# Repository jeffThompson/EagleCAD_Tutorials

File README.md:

EagleCAD Tutorials
==================

A set of tutorials for learning EagleCAD and circuit design.

####DRU FILE
Also included is a design rule set called 'BasicHandEtching.dru', designed for home PCB etching using laser printed overhead transparencies and ferric chloride. To install this file, download it and place it in:

    Applications > Eagle > dru

####PCB ETCHING IMAGE
This repository also includes a file called 'PCB_EtchingImage.png' - this file has undergone several transformations after export from Eagle:
1. Colors inverted - I use a MG Chemicals 600 series boards which are positive sensitized. Areas that are white are exposed and etched away, so the image from Eagle must be inverted.
2. The image is flipped - this means that when printed on overhead transparency film the printed image will be face-down, ensuring no light leaks under the printed image.

\- \- \-

\[ all code available under [Creative Commons BY-NC-SA license](http://creativecommons.org/licenses/by-nc-sa/3.0/) - feel free to use but [please let me know](http://www.jeffreythompson.org) \]

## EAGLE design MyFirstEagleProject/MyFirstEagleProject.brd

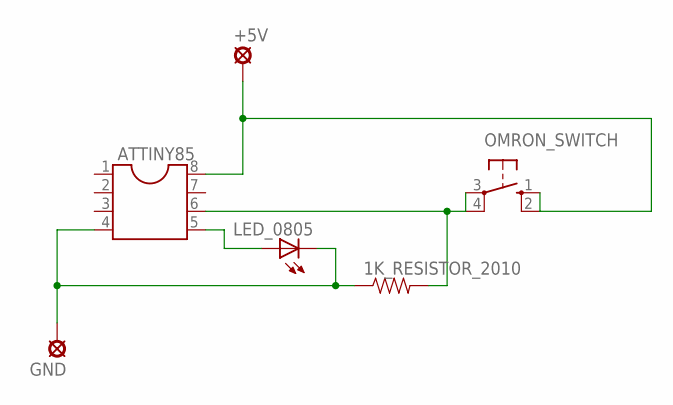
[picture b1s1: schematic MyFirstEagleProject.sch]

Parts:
1K_RESISTOR_2010: RESISTOR2010; R2010
+5V: SE14
ATTINY85: DIL8S; SOCKET-08
GND: SE14
LED_0805: LEDCHIPLED_0805; CHIPLED_0805
OMRON_SWITCH: 10-XX; B3F-10XX

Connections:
5V: +5V.MP, ATTINY85.8, OMRON_SWITCH.1 (S), OMRON_SWITCH.2 (S1)
GND: 1K_RESISTOR_2010.1, ATTINY85.4, GND.MP, LED_0805.C
unnamed: ATTINY85.5, LED_0805.A
unnamed: 1K_RESISTOR_2010.2, ATTINY85.6, OMRON_SWITCH.3, OMRON_SWITCH.4 (P1)

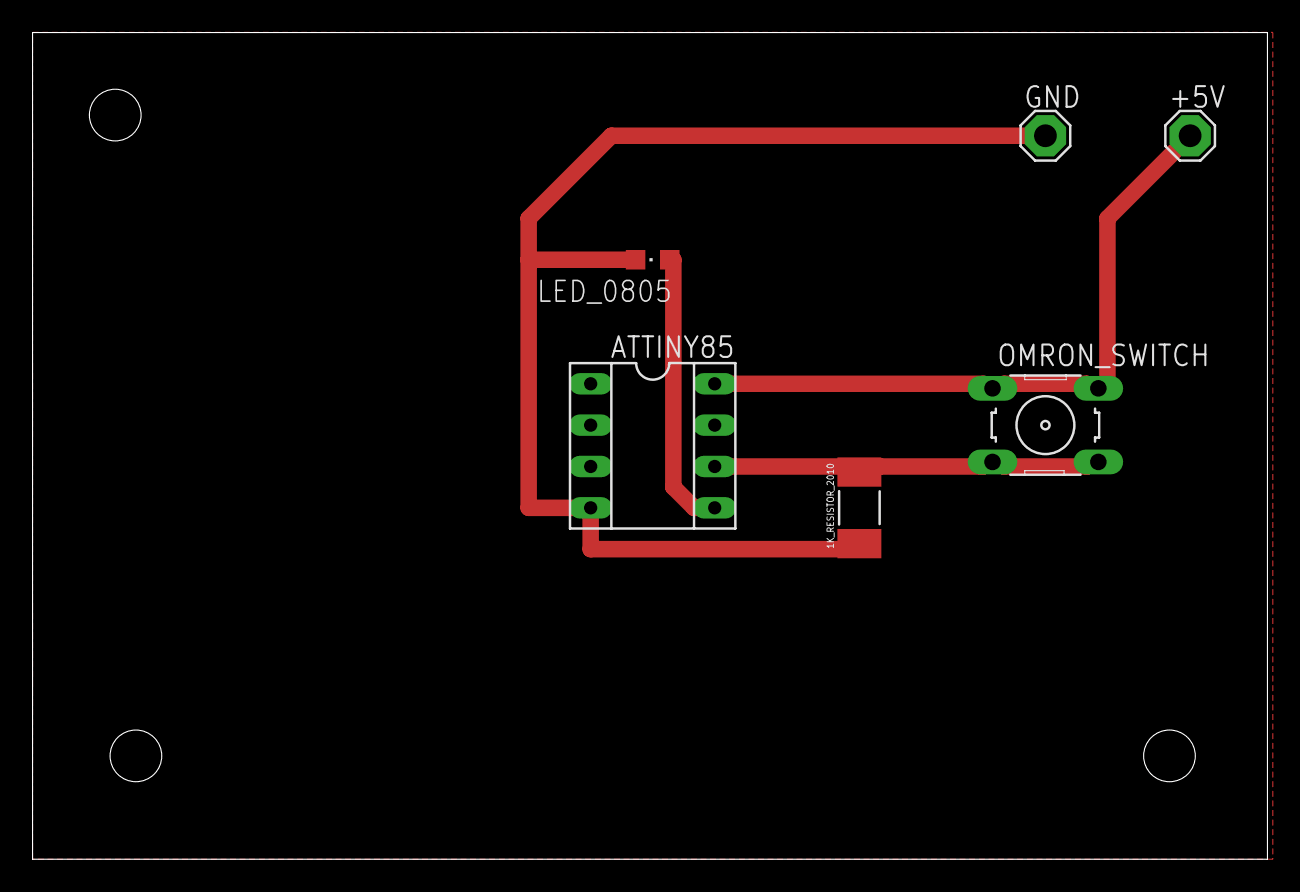
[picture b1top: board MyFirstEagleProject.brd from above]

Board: 2 copper layers, 75.9 x 50.8 mm, 6 parts (0 on the bottom side), 4 nets.

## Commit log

2013-03-14 Updated schematic/PCB files
2013-03-26 Minor PCB fixes, added PCB layout for printing

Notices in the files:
parts and their libraries:
SparkFun: Licensing: CC v3.0 Share-Alike You are welcome to use this library for commercial purposes.
